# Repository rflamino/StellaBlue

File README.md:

# StellaBlue

StellaBlue AKA Retro2600: An FPGA clone of the Atari 2600 based on [Retromaster]'s cores.

-------------------------------------------------------------------------------

This project aims to use the hardware with the original atari cartridge configuration. Additionaly, the board also supports the original Paddle Controller (not fully tested) and the standard one.

The quartus project contains the glue logic to join the Retromaster's cores to the hardware (EP2C5T144 board - AKA "cheap FPGA blue board").

Using a fpga blaster; upload the "retro2600.pof" file via "Active Serial Programming". The device is EPCS4. Check the programming options "Program/Configure; Verifiy and Blank-Check".

The file "CartridgeGuide.stl" contains a Cartridge Guide socket. Print it! - with a 3D printer :)

rflamino AKA (Reinaldo de Sales Flamino)
Website:	[hackaday.io/rflamino]
email:		reinaldosflamino@gmail.com

[Danjovic]  AKA (Daniel Jose Viana)
Websites:	[danjovic.blogspot.com] & [hackaday.io/danjovic]
email:		danjovic@hotmail.com

[Danjovic]: <https://hackaday.io/danjovic/>
[hackaday.io/rflamino]: <https://hackaday.io/rflamino/>
[danjovic.blogspot.com]: <https://danjovic.blogspot.com/>
[hackaday.io/danjovic]: <https://hackaday.io/danjovic/>
[Danjovic]: <https://github.com/Danjovic/>
[Retromaster]: <https://retromaster.wordpress.com/a2601/>

First PCB!

![alt text](https://github.com/rflamino/StellaBlue/blob/master/pictures/StellaBlue.jpg
)

Working!

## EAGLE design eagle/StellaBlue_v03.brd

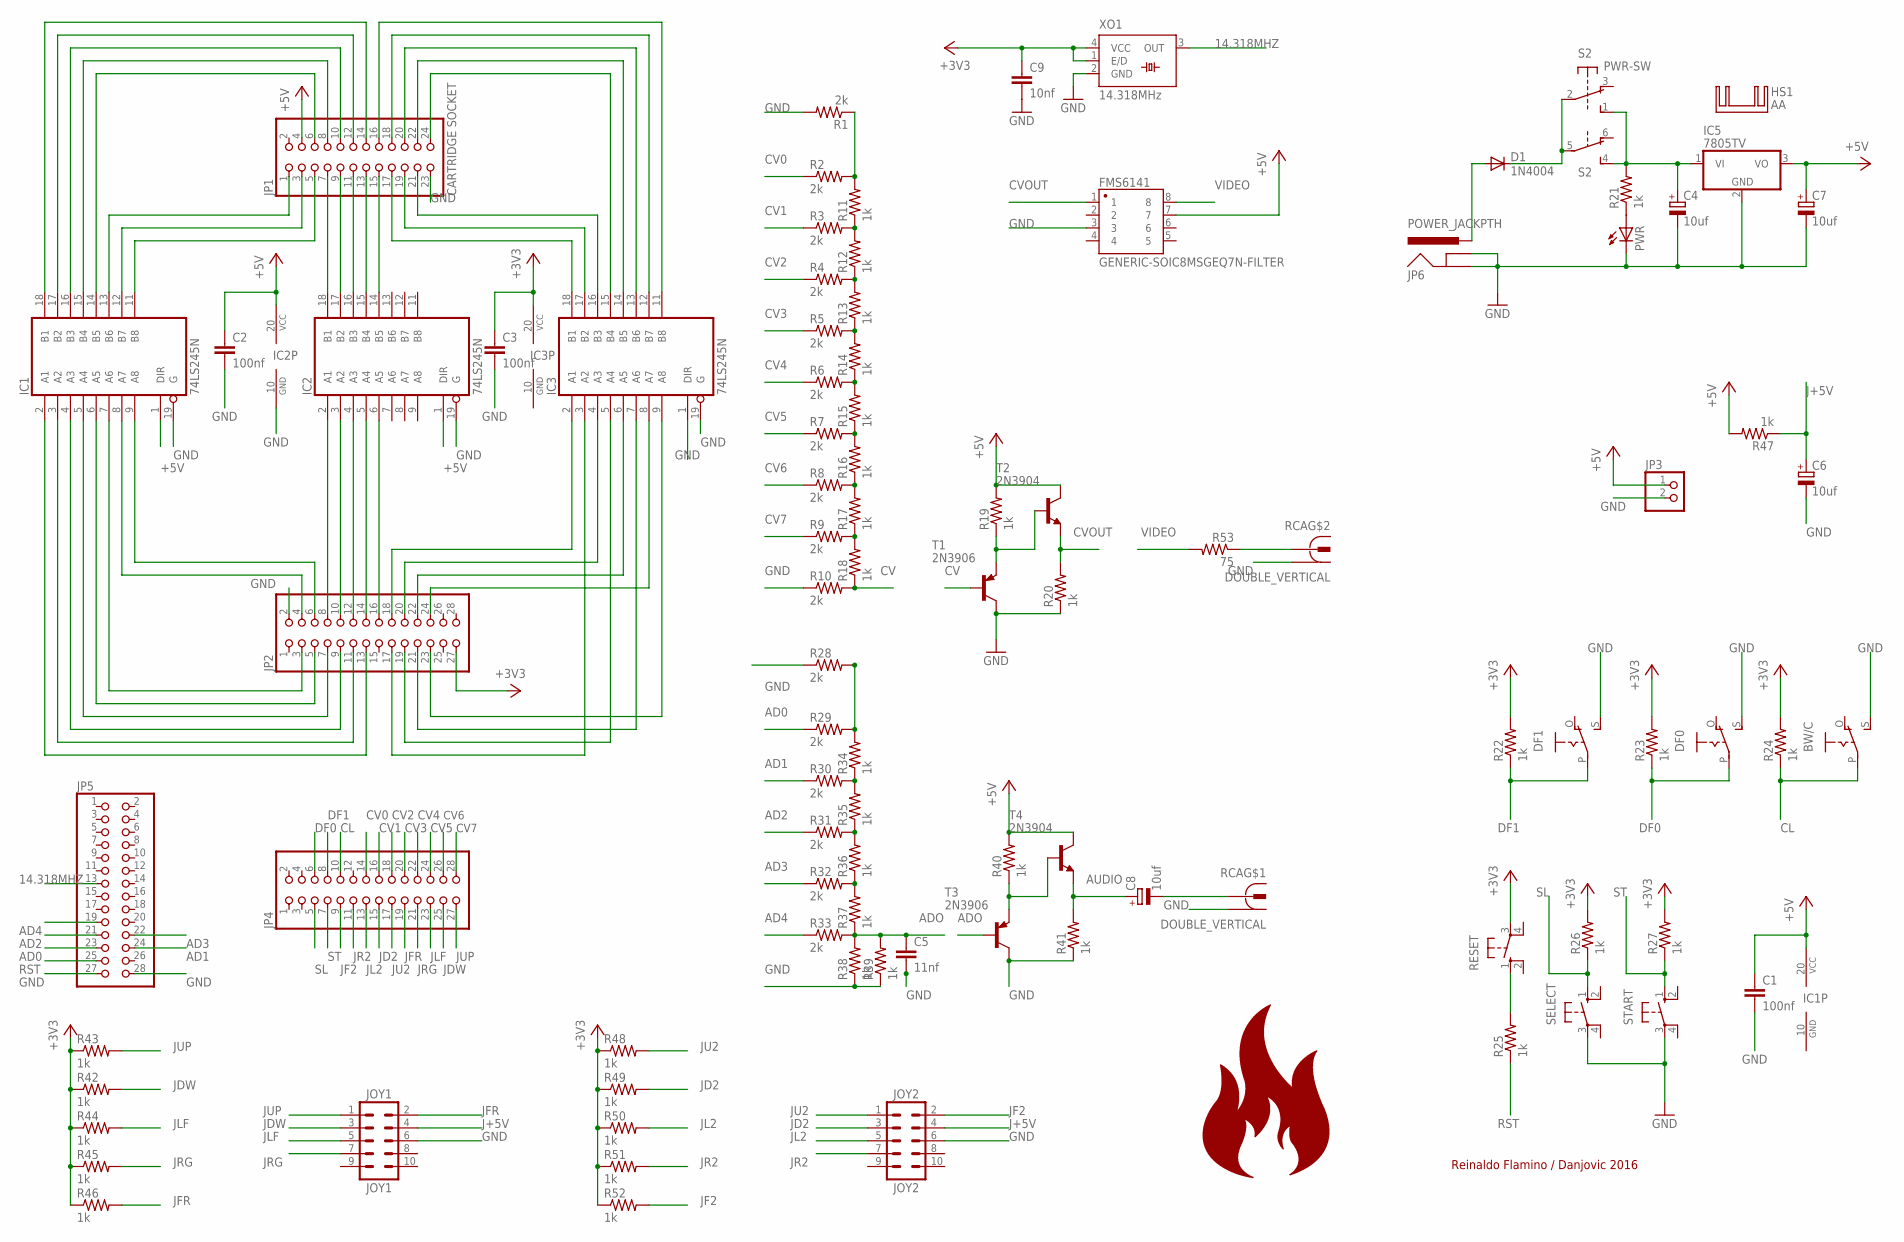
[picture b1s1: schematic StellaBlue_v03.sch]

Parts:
BW/C: EG1218S; EG1218
C1, C2, C3: 100nf; C5B2.5
C4, C7, C8: 10uf; E2,5-6
C5: 11nf; C5B2.5
C6: 10uf; TT2D6
C9: 10nf; C5B2.5
D1: 1N4004; DO41-10
DF0, DF1: EG1218S; EG1218
FMS6141: GENERIC-SOIC8MSGEQ7N-FILTER; SO08
HS1: AA
IC1, IC2, IC3: 74LS245N; DIL20
IC5: 7805TV; TO220V
JOY1: JOY1; 2X5-SHROUDED_LOCK
JOY2: JOY2; 2X5-SHROUDED_LOCK
JP1: CARTRIDGE SOCKET; ATARI2600_SLOT
JP2, JP4, JP5: PINHD-2X14; 2X14
JP3: PINHD-1X2/90; 1X02/90
JP6: POWER_JACKPTH; POWER_JACK_PTH
PWR: LED3MM
R1, R2, R3, R4, R5, R6, R7, R8, R9, R10, R28, R29, R30, R31, R32, R33: 2k; 0207/7
R11, R12, R13, R14, R15, R16, R17, R18, R19, R20, R21, R22, R23, R24, R25, R26, R27, R34, R35, R36, R37, R38, R39, R40, R41, R42, R43, R44, R45, R46, R47, R48, R49, R50, R51, R52: 1k; 0207/7
R53: 75; 0207/7
RCA: DOUBLE_VERTICAL; DOUBLE-VERTICAL
RESET: 10-XX; B3F-10XX
S2: PWR-SW; 9077-2
SELECT: 10-XX; B3F-10XX
START: 10-XX; B3F-10XX
T1, T3: 2N3906; TO92-EBC
T2, T4: 2N3904; TO92-EBC
XO1: 14.318MHz; SM77H

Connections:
14.318MHZ: JP5.13, XO1.3 (OUT)
+3V3: C3.1, C9.1, IC3.20 (VCC), JP2.27, R22.2, R23.2, R24.2, R26.2, R27.2, R42.1, R43.1, R44.1, R45.1, R46.1, R48.1, R49.1, R50.1, R51.1, R52.1, RESET.3, XO1.1 (E/D), XO1.4 (VCC)
+5V: C1.1, C2.1, C7.+, FMS6141.7, IC1.1 (DIR), IC1.20 (VCC), IC2.1 (DIR), IC2.20 (VCC), IC5.3 (VO), JP1.4, JP3.1, R19.2, R40.2, R47.2, T2.C, T4.C
AD0: JP5.23, R29.1
AD1: JP5.24, R30.1
AD2: JP5.21, R31.1
AD3: JP5.22, R32.1
AD4: JP5.19, R33.1
ADO: C5.1, R33.2, R37.1, R38.2, R39.2, T3.B
AUDIO: C8.+, R41.2, T4.E
CL: BW/C.P, JP4.10, R24.1
CV: R10.2, R18.1, T1.B
CV0: JP4.14, R2.1
CV1: JP4.16, R3.1
CV2: JP4.18, R4.1
CV3: JP4.20, R5.1
CV4: JP4.22, R6.1
CV5: JP4.24, R7.1
CV6: JP4.26, R8.1
CV7: JP4.28, R9.1
CVOUT: FMS6141.1, R20.2, T2.E
DF0: DF0.P, JP4.6, R23.1
DF1: DF1.P, JP4.8, R22.1
GND: BW/C.S, C1.2, C2.2, C3.2, C4.-, C5.2, C6.-, C7.-, C9.2, DF0.S, DF1.S, FMS6141.3, IC1.10 (GND), IC1.19 (G), IC2.10 (GND), IC2.19 (G), IC3.1 (DIR), IC3.10 (GND), IC3.19 (G), IC5.2 (GND), JOY1.6, JOY2.6, JP1.23, JP2.2, JP3.2, JP5.27, JP5.28, JP6.GND, JP6.GNDBREAK, PWR.K (C), R1.2, R10.1, R20.1, R28.1, R38.1, R39.1, R41.1, RCA.HG (1), RCA.LG (1), SELECT.3, START.3, T1.C, T3.C, XO1.2 (GND)
J+5V: C6.+, JOY1.4, JOY2.4, R47.1
JD2: JOY2.3, JP4.15, R49.2
JDW: JOY1.3, JP4.25, R42.2
JF2: JOY2.2, JP4.9, R52.2
JFR: JOY1.2, JP4.19, R46.2
JL2: JOY2.5, JP4.13, R50.2
JLF: JOY1.5, JP4.23, R44.2
JR2: JOY2.7, JP4.11, R51.2
JRG: JOY1.7, JP4.21, R45.2
JU2: JOY2.1, JP4.17, R48.2
JUP: JOY1.1, JP4.27, R43.2
unnamed: IC1.18 (B1), JP1.14
unnamed: IC1.17 (B2), JP1.12
unnamed: IC1.16 (B3), JP1.10
unnamed: IC1.15 (B4), JP1.8
unnamed: IC1.14 (B5), JP1.6
unnamed: IC1.13 (B6), JP1.1
unnamed: IC1.12 (B7), JP1.3
unnamed: IC1.11 (B8), JP1.5
unnamed: IC2.18 (B1), JP1.7
unnamed: IC2.17 (B2), JP1.9
unnamed: IC2.16 (B3), JP1.11
unnamed: IC2.15 (B4), JP1.13
unnamed: IC2.14 (B5), JP1.15
unnamed: IC3.18 (B1), JP1.17
unnamed: IC3.17 (B2), JP1.19
unnamed: IC3.16 (B3), JP1.21
unnamed: IC3.15 (B4), JP1.24
unnamed: IC3.14 (B5), JP1.22
unnamed: IC3.13 (B6), JP1.20
unnamed: IC3.12 (B7), JP1.18
unnamed: IC3.11 (B8), JP1.16
unnamed: IC1.2 (A1), JP2.13
unnamed: IC1.3 (A2), JP2.11
unnamed: IC1.4 (A3), JP2.9
unnamed: IC1.5 (A4), JP2.7
unnamed: IC1.6 (A5), JP2.5
unnamed: IC1.7 (A6), JP2.3
unnamed: IC1.8 (A7), JP2.4
unnamed: IC1.9 (A8), JP2.6
unnamed: IC2.2 (A1), JP2.8
unnamed: IC2.3 (A2), JP2.10
unnamed: IC2.4 (A3), JP2.12
unnamed: IC2.5 (A4), JP2.14
unnamed: IC2.6 (A5), JP2.16
unnamed: IC3.2 (A1), JP2.18
unnamed: IC3.3 (A2), JP2.17
unnamed: IC3.4 (A3), JP2.20
unnamed: IC3.5 (A4), JP2.19
unnamed: IC3.6 (A5), JP2.22
unnamed: IC3.7 (A6), JP2.21
unnamed: IC3.8 (A7), JP2.24
unnamed: IC3.9 (A8), JP2.23
unnamed: D1.A, JP6.PWR
unnamed: D1.C, S2.2, S2.5
unnamed: R1.1, R2.2, R11.2
unnamed: R3.2, R11.1, R12.2
unnamed: R53.1, RCA.LS (2)
unnamed: C4.+, IC5.1 (VI), R21.2, S2.1 (S), S2.4 (S)
unnamed: R4.2, R12.1, R13.2
unnamed: R5.2, R13.1, R14.2
unnamed: R6.2, R14.1, R15.2
unnamed: R7.2, R15.1, R16.2
unnamed: R8.2, R16.1, R17.2
unnamed: R9.2, R17.1, R18.2
unnamed: R19.1, T1.E, T2.B
unnamed: PWR.A, R21.1
unnamed: R25.2, RESET.1 (S)
unnamed: R28.2, R29.2, R34.2
unnamed: R30.2, R34.1, R35.2
unnamed: R31.2, R35.1, R36.2
unnamed: R32.2, R36.1, R37.2
unnamed: R40.1, T3.E, T4.B
unnamed: C8.-, RCA.HS (2)
RST: JP5.25, R25.1
SL: JP4.5, R26.1, SELECT.1 (S)
ST: JP4.7, R27.1, START.1 (S)
VIDEO: FMS6141.8, R53.2

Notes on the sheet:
Reinaldo Flamino / Danjovic 2016

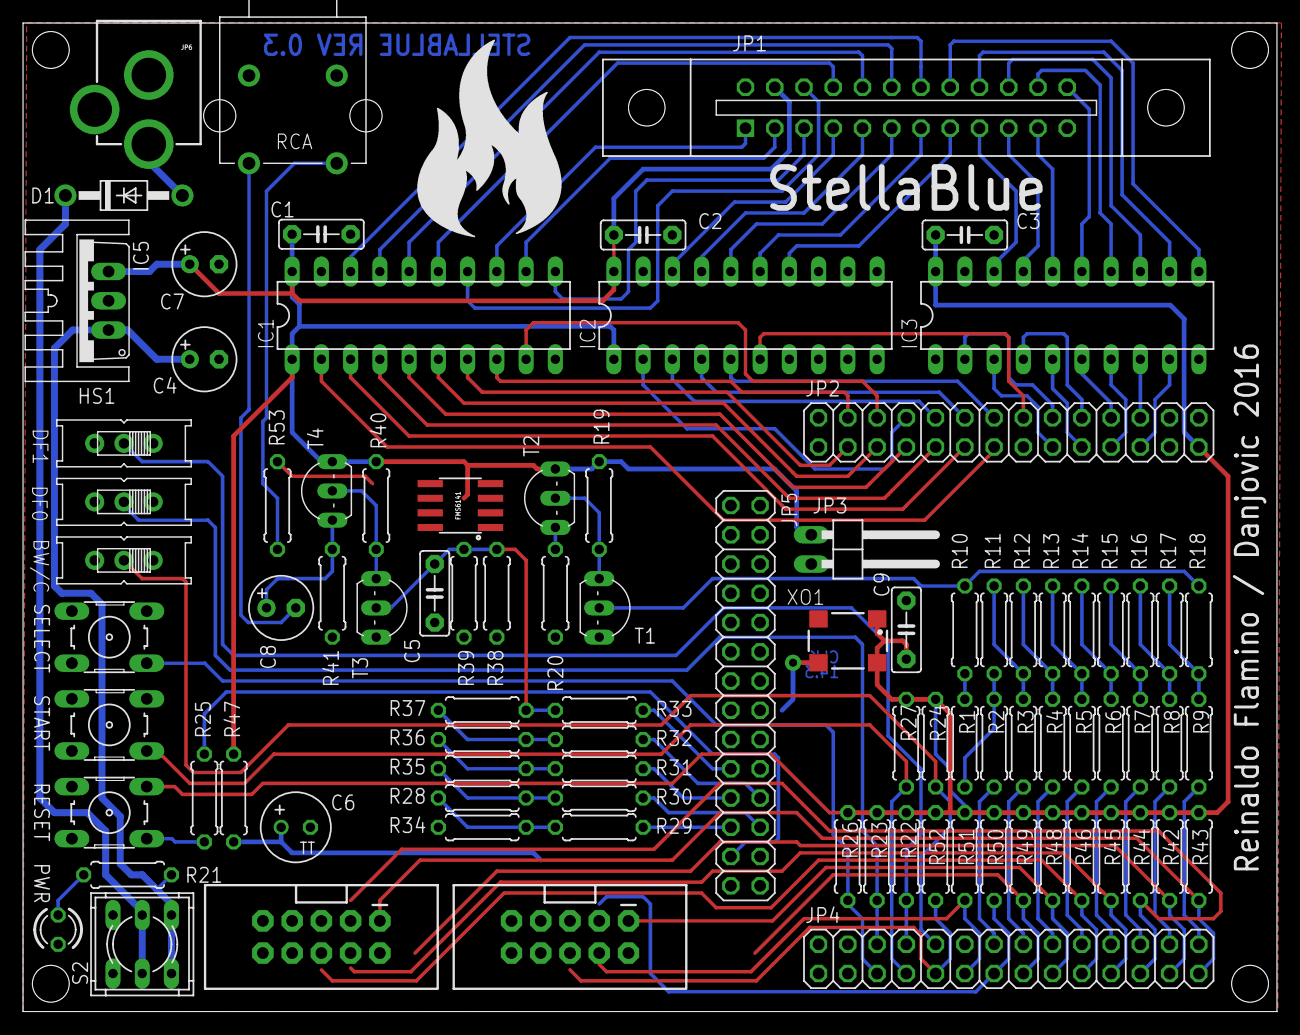
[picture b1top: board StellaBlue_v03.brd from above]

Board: 2 copper layers, 108.9 x 85.8 mm, 91 parts (0 on the bottom side), 102 nets.

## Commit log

2016-08-31 first release
2016-09-01 PCB layout manual enhancements. Still in progress
2016-09-02 Finished PCB routing, label placement still in work
2016-09-03 labels replacement
2016-09-03 labels positioning
2016-09-05 Corrected board dimentions
    Daniel favor verificar
2016-09-05 Corrected board dimension
    issue came from repositioning Labels
2016-09-05 .gitignore
2016-09-05 First PCB routing !
2016-10-08 Added 14.318MHz crystal oscillator
2016-11-06 Corrected FMS6141, Joysticks, Crystal Oscillator pinouts
    Corrected FMS6141 pinout (library was wrong)
    Corrected Joysticks pinouts
    Changed Crystal Oscillator to port 91 of FPGA
2016-11-06 temp files deleted
2016-11-06 stellablue core
2016-11-26 Added script to generate RCA connector footprint
2018-07-15 Rename StellaBlue.brd to StellaBlue_v03.brd
2018-09-08 recompiled core
2018-09-16 parts
2018-09-16 project update
2018-09-16 core upload
2018-09-16 description update
2018-09-16 more descriptions
2018-09-16 more description
2018-09-17 more description details
2018-09-17 descriptions
2018-09-17 descriptions and stl file
2018-09-17 pictures
2018-09-17 picture
2018-09-18 stellablue picture

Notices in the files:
parts and their libraries:
SparkFun-Connectors: Licensing: Creative Commons ShareAlike 4.0 International - https://creativecommons.org/licenses/by-sa/4.0
